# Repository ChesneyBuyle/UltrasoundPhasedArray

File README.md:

# UltrasoundPhasedArray
 Ultrasound phased array for directional transmission: construction, embedded software and python implementation

## General specifications
A low-cost, narrowband ultrasound phased array system for narrowbeam transmission is presented. 

The design features wide bandwidth MEMS loudspeakers (UT-P 2019, USound) with very small dimensions (5 x 7 mm). Dense loudspeaker arrays with small interelement spacing can be constructed, enabling grating lobe free beam patterns at high frequency. The current prototype can support up to 64 MEMS speakers. The amplitude and phase of each loudspeaker stage can be controlled with high resolution, respectively with 10-bit and 12-bit. The array itself is constructed using a 3D printer. 

## System overview

Block diagram of the prototype:

The loudspeaker array is controlled by an external computer. The phase delays and amplitudes of the loudspeaker stages are calculated according to the desired ultrasound beam pattern in Python. Next, these parameters are sent to a controller board, which consists of a NUCLEO-H743ZI2 microcontroller board and custom signal distribution PCB. 
* The microcontroller sends the transducer stage parameters to the corresponding DSP boards. The DSP boards contain the signal generation and amplifier hardware blocks of the loudspeaker stages. 
* The microcontroller uses the signal distribution board to distribute a common clock signal to the DSP boards (for phase coherence) and it ensures communication to the correct hardware blocks. 

## Folder structure
* The *3D prints* folder contains the necessary STL-files to print the array. The loudspeakers should first be placed inside the *holder part (part 1)*. Next, the *cover part (part 2)* can be attached to the back of the array (side with connections on the MEMS loudspeakers) using M2 bolts. This keeps the MEMS loudspeakers in place when soldering the signal wires. Hence, now you should be able to solder the signal wires to the loudspeaker elements. We used very thin 0.25mm coated copper wire, because the loudspeaker connections are very fragile. Finally, we placed a thin layer of acoustic foam on the back of array and kept it into place using the *wire cover part (part 3)*. It also ensures that the signal wires and thus MEMS loudspeakers do not move anymore. 

* The *Python* folder contains the Python scripts for control over the transducer stages (controller.py and main.py). Furthermore, the Python scripts for sampling of the microphone signal (daq.py), stepper motor control (stepper.py) and plotting (plotter.py) are also available. Note that some paths may need to updated before the code runs correctly.

* The *PCB design files* folder contains the schematic and board files of the custom signal distribution and DSP boards (DDS, VGA and power amplifier). These were designed in Eagle. 

* The *Controller board code* contains the embedded code for the NUCLEO-H743ZI2 microcontroller board.

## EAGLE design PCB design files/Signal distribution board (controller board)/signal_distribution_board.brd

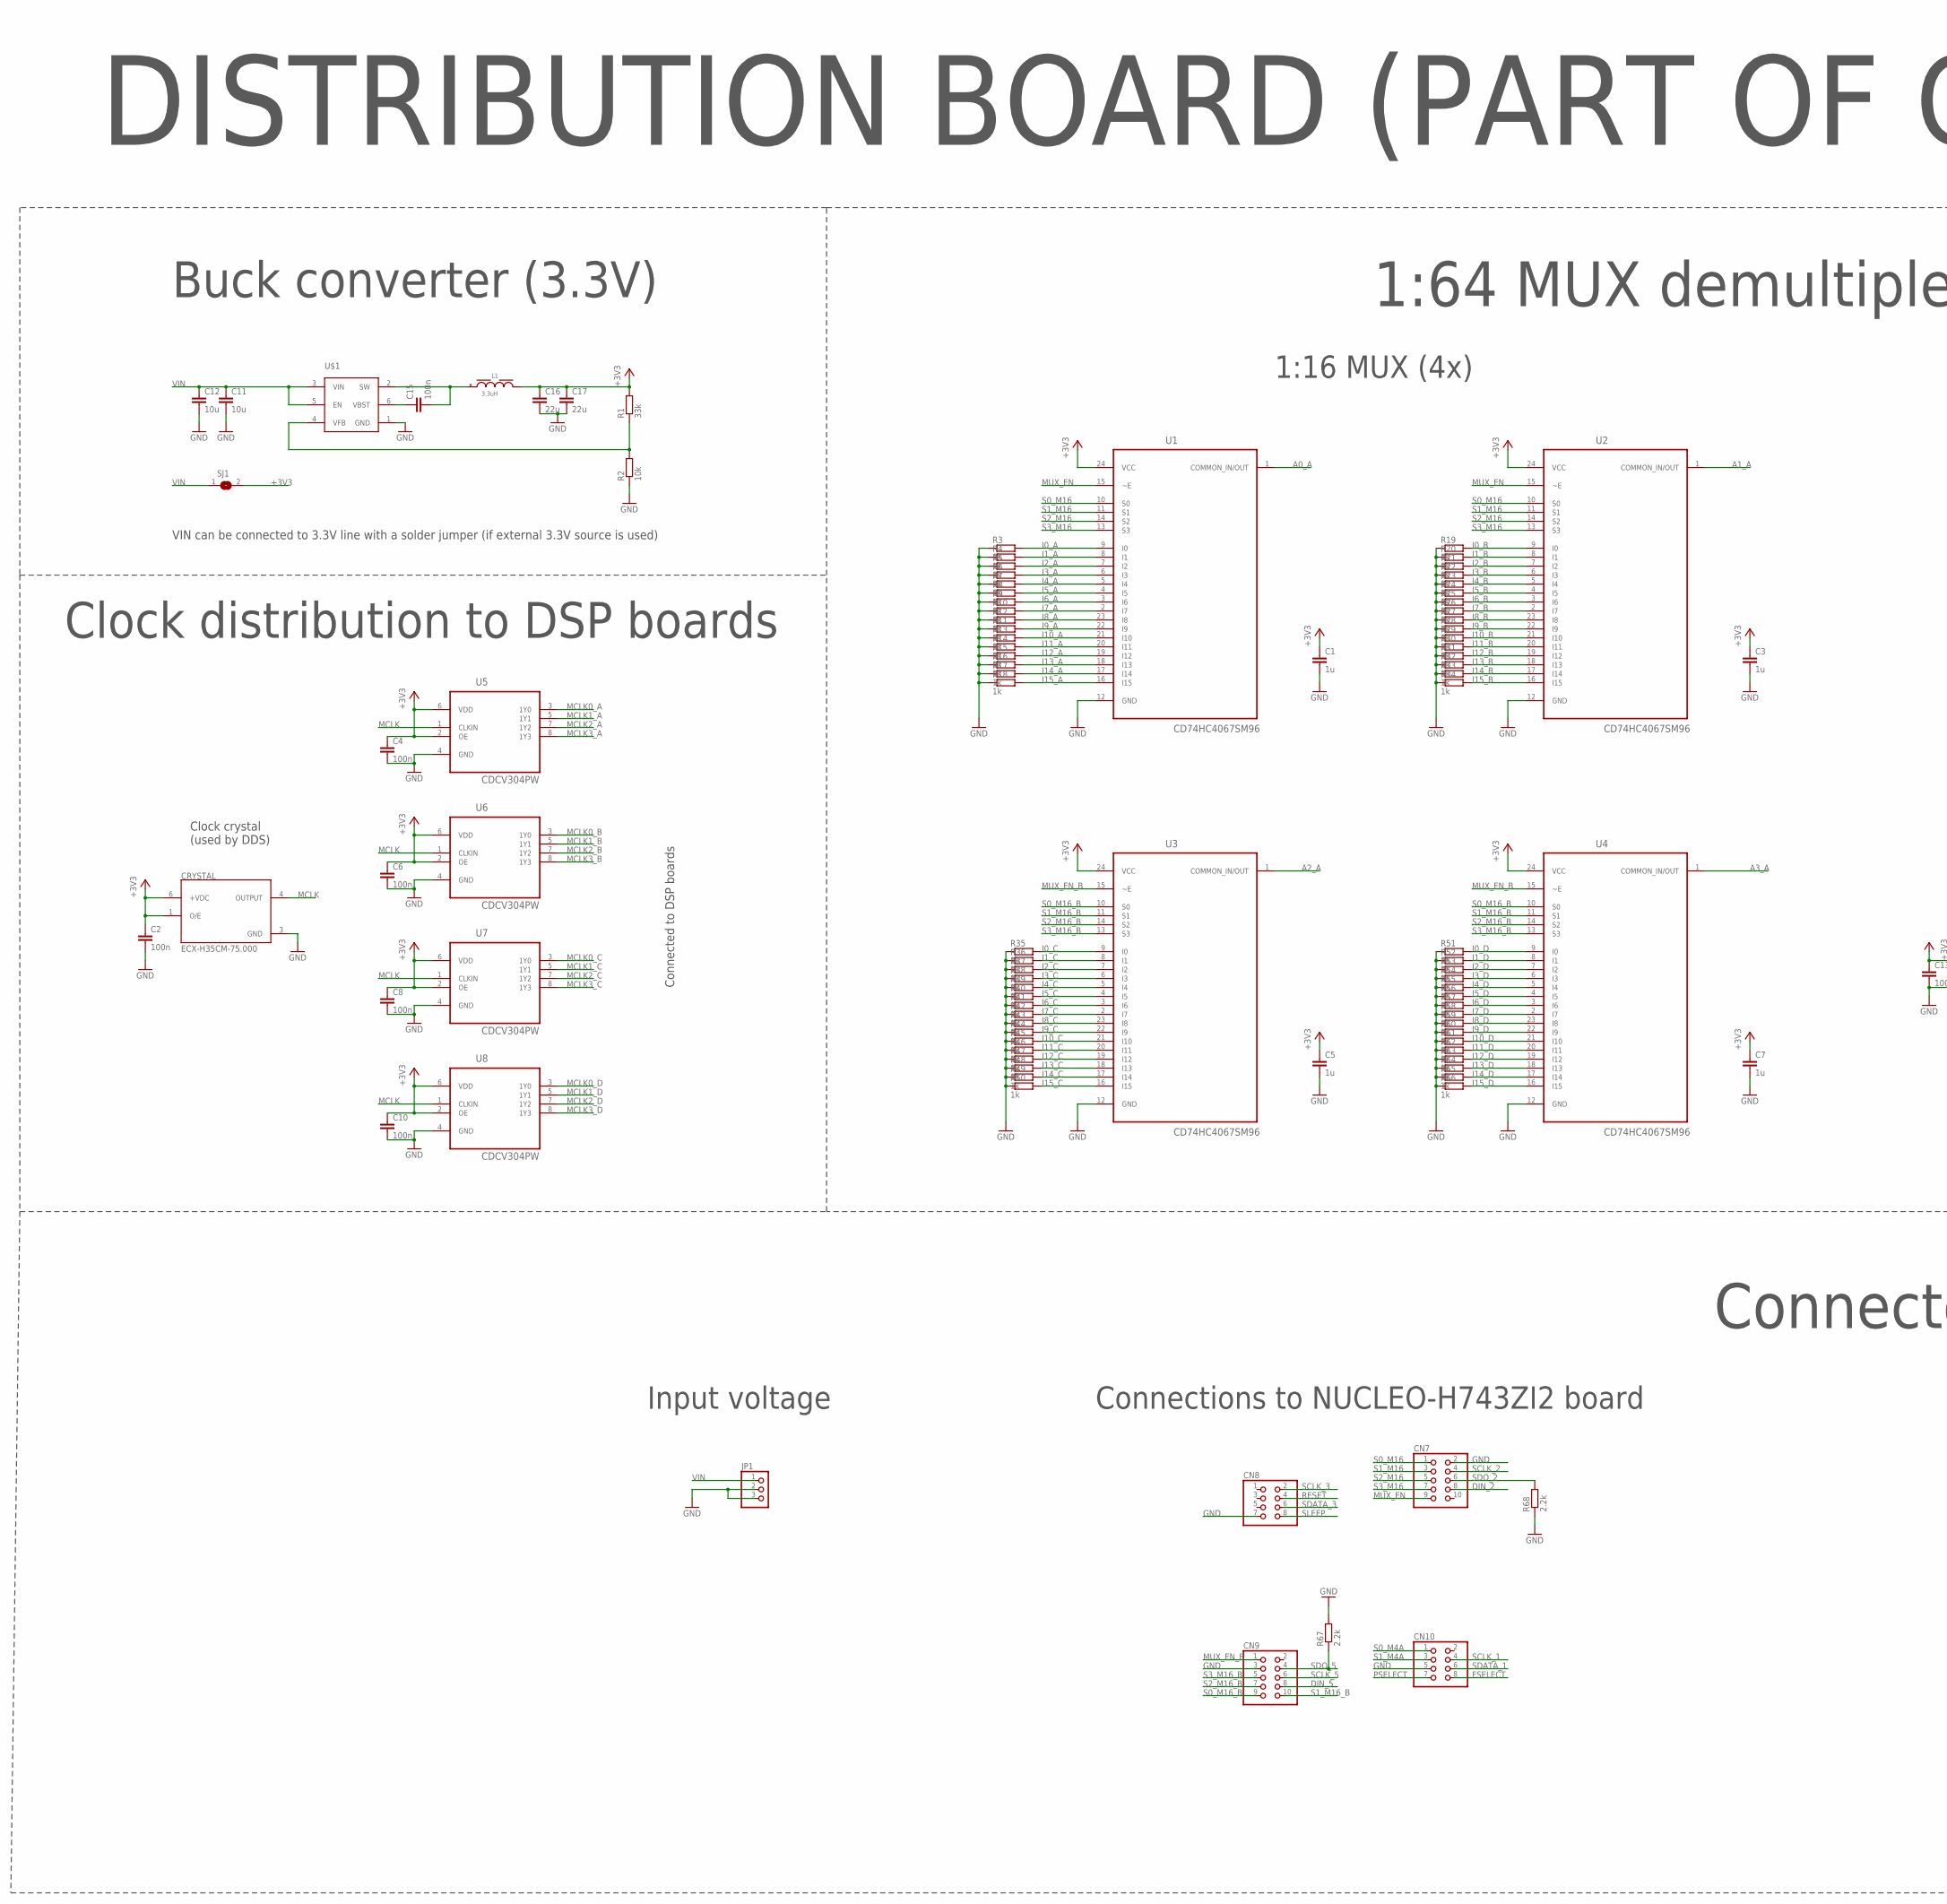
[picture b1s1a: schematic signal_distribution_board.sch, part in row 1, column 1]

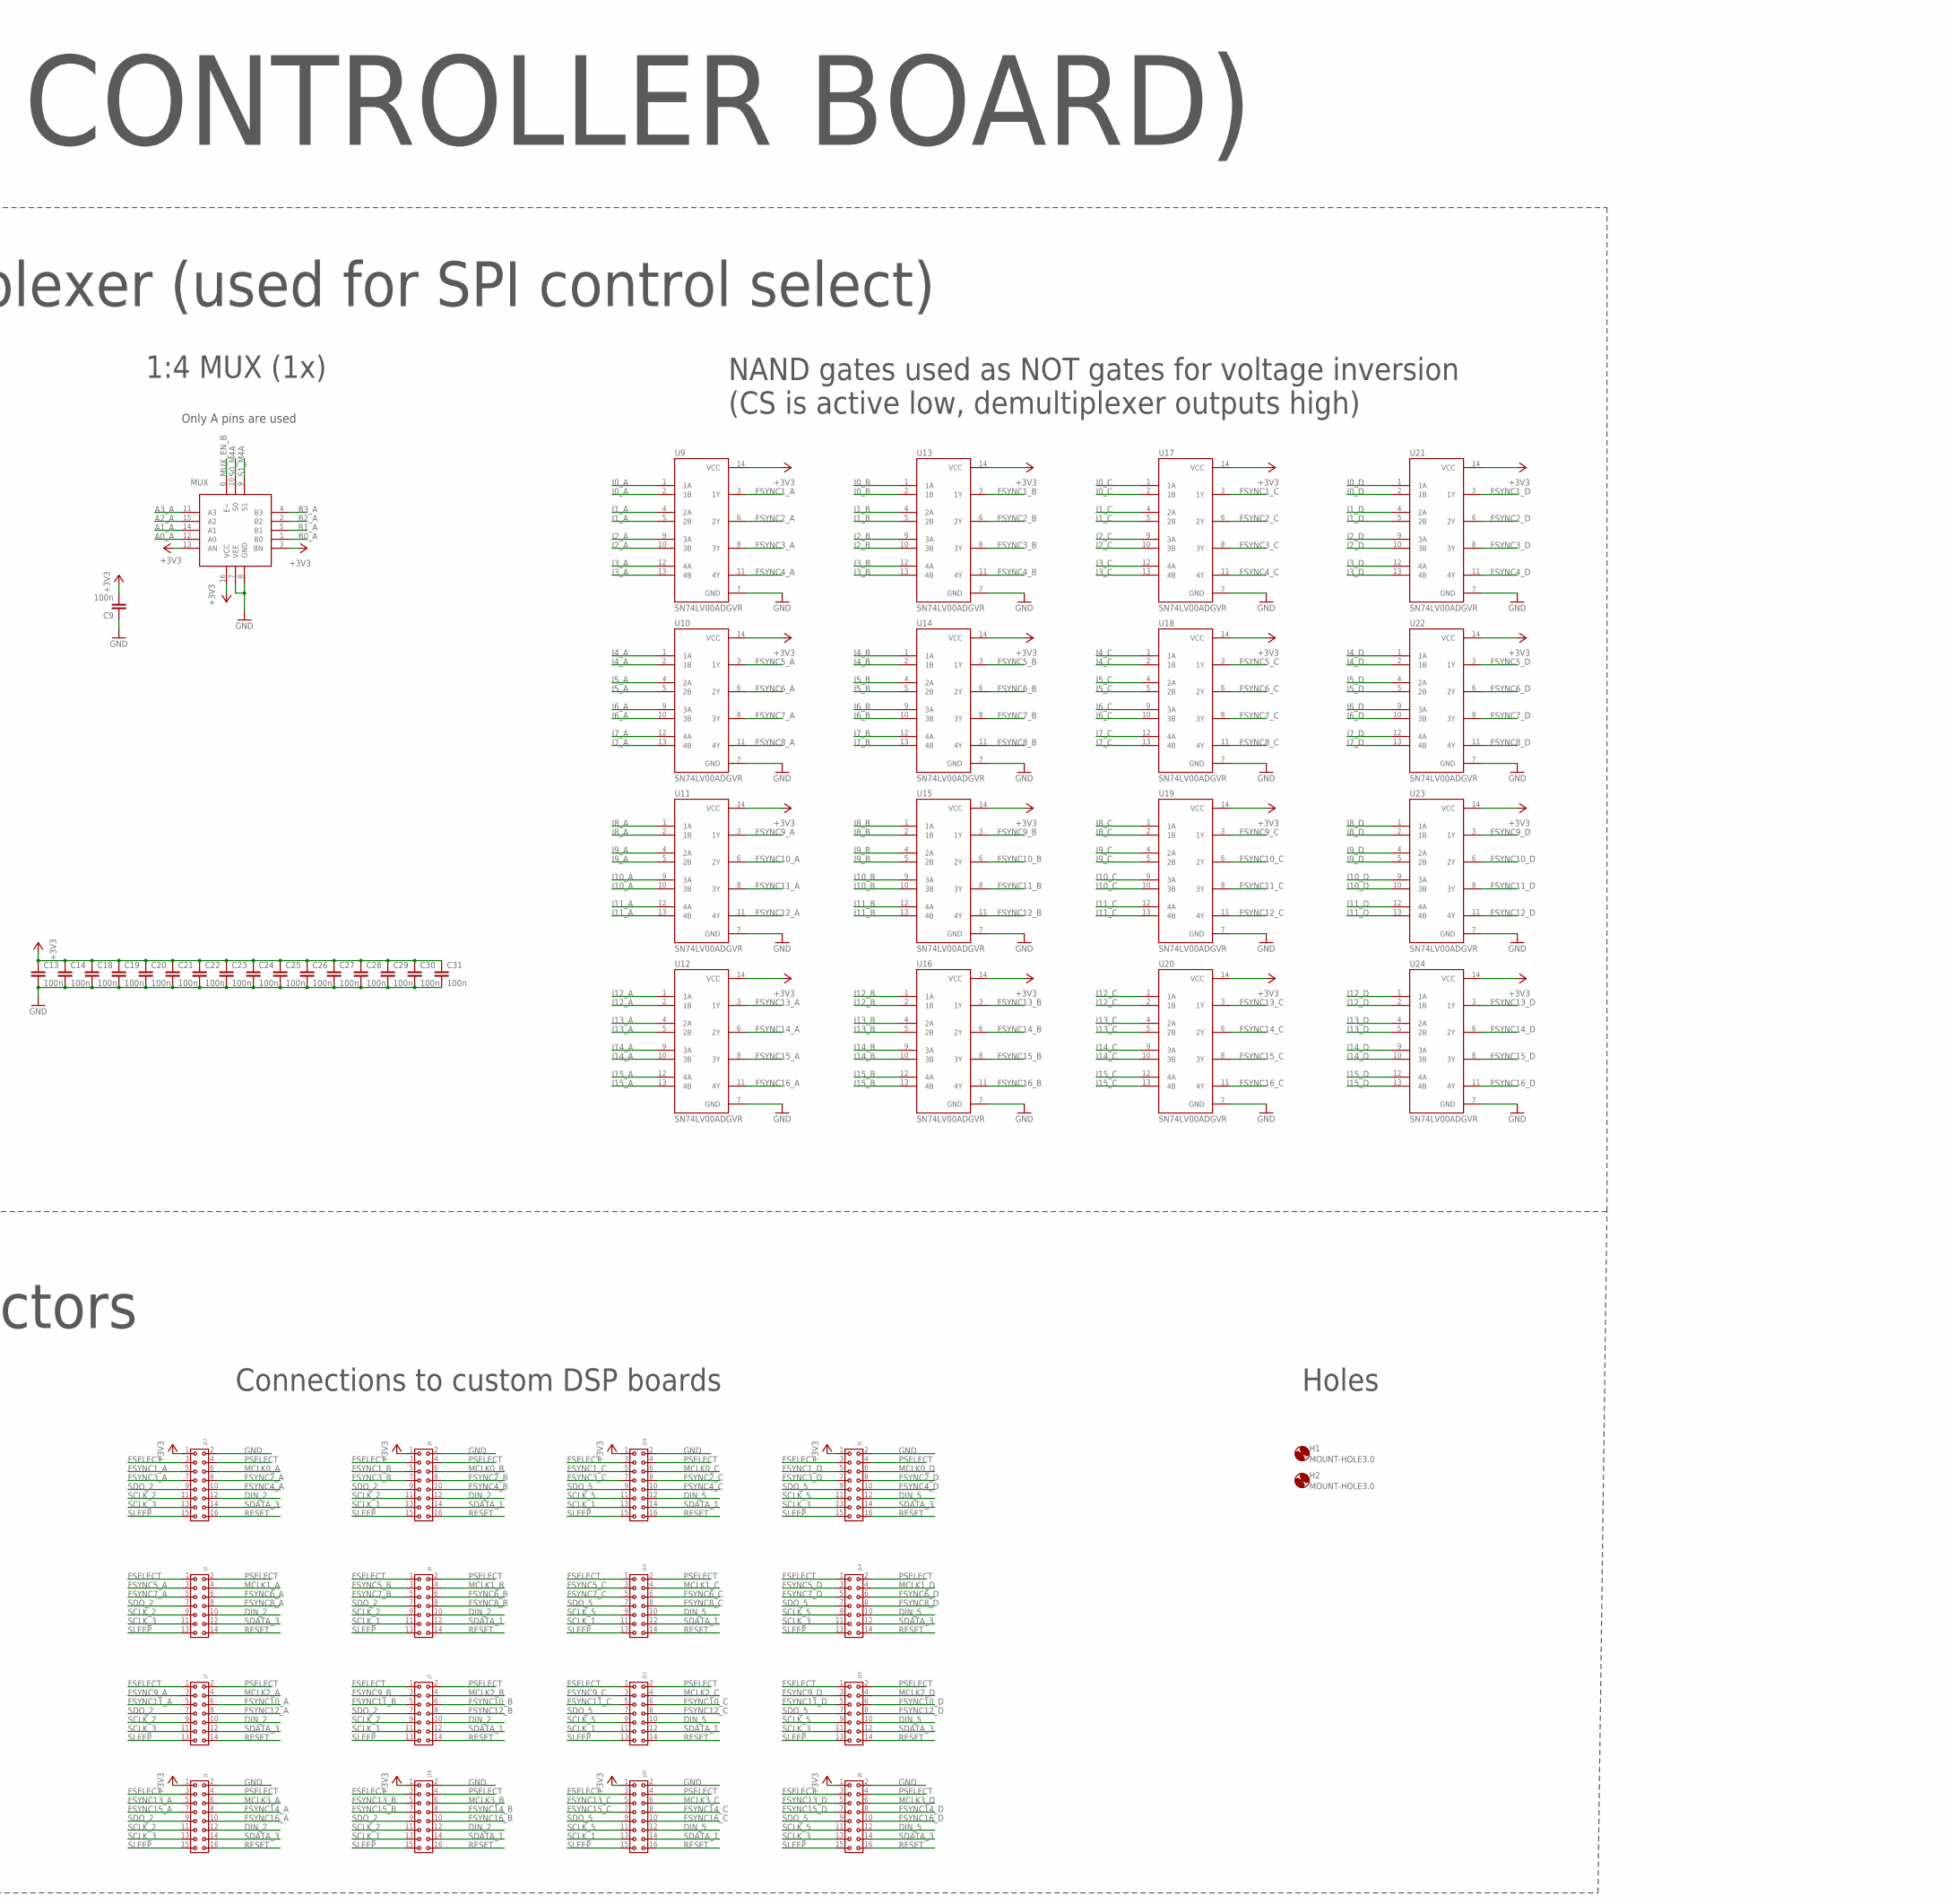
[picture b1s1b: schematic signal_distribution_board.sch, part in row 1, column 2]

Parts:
C1, C3, C5, C7: 1u; C0603
C2, C4, C6, C8, C9, C10, C13, C14, C15, C18, C19, C20, C21, C22, C23, C24, C25, C26, C27, C28, C29, C30, C31: 100n; C0603
C11, C12: 10u; C0805
C16, C17: 22u; C1206
CN7, CN9: PINHD-2X5; 2X05
CN8, CN10: PINHD-2X4; 2X04
CRYSTAL: ECX-H35CM-75.000; OSC_ECX-H35CM-75.000
H1, H2: MOUNT-HOLE3.0; 3,0
J1, J4, J5, J8, J17, J18, J19, J20: 6130XX243121_613016243121; 613016243121
J2, J3, J6, J7, J10, J11, J14, J15: 6130XX243121_613014243121; 613014243121
JP1: PINHD-1X3; 1X03
L1: 3.3uH; WE-PD_7345P
MUX: CD74HC4052M96; SOIC127P600X175-16N
R1: 33k; R0603
R2: 10k; R0603
R3, R4, R5, R6, R7, R8, R9, R10, R11, R12, R13, R14, R15, R16, R17, R18, R19, R20, R21, R22, R23, R24, R25, R26, R27, R28, R29, R30, R31, R32, R33, R34, R35, R36, R37, R38, R39, R40, R41, R42, R43, R44, R45, R46, R47, R48, R49, R50, R51, R52, R53, R54, R55, R56, R57, R58, R59, R60, R61, R62, R63, R64, R65, R66: 1k; R0603
R67, R68: 2.2k; R0805
SJ1: SJ
U1, U2, U3, U4: CD74HC4067SM96; SOP65P780X200-24N
U5, U6, U7, U8: CDCV304PW; SOP65P640X120-8N
U9, U10, U11, U12, U13, U14, U15, U16, U17, U18, U19, U20, U21, U22, U23, U24: SN74LV00ADGVR; SOP40P640X120-14N
U$1: TPS562209; SOT95P280X110-6N

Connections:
+3V3: C1.1, C2.1, C3.1, C4.1, C5.1, C6.1, C7.1, C8.1, C9.2, C10.1, C13.1, C14.1, C16.1, C17.1, C18.1, C19.1, C20.1, C21.1, C22.1, C23.1, C24.1, C25.1, C26.1, C27.1, C28.1, C29.1, C30.1, C31.1, CRYSTAL.1 (O/E), CRYSTAL.6 (+VDC), J1.1, J4.1, J5.1, J8.1, J17.1, J18.1, J19.1, J20.1, L1.2, MUX.3 (BN), MUX.13 (AN), MUX.16 (VCC), R1.2, SJ1.2, U1.24 (VCC), U2.24 (VCC), U3.24 (VCC), U4.24 (VCC), U5.2 (OE), U5.6 (VDD), U6.2 (OE), U6.6 (VDD), U7.2 (OE), U7.6 (VDD), U8.2 (OE), U8.6 (VDD), U9.14 (VCC), U10.14 (VCC), U11.14 (VCC), U12.14 (VCC), U13.14 (VCC), U14.14 (VCC), U15.14 (VCC), U16.14 (VCC), U17.14 (VCC), U18.14 (VCC), U19.14 (VCC), U20.14 (VCC), U21.14 (VCC), U22.14 (VCC), U23.14 (VCC), U24.14 (VCC)
A0_A: MUX.12 (A0), U1.1 (COMMON_IN/OUT)
A1_A: MUX.14 (A1), U2.1 (COMMON_IN/OUT)
A2_A: MUX.15 (A2), U3.1 (COMMON_IN/OUT)
A3_A: MUX.11 (A3), U4.1 (COMMON_IN/OUT)
B0_A: MUX.1 (B0)
B1_A: MUX.5 (B1)
B2_A: MUX.2 (B2)
B3_A: MUX.4 (B3)
DIN_2: CN7.8, J1.12, J2.10, J3.10, J4.12, J6.10, J7.10, J17.12, J18.12
DIN_5: CN9.8, J5.12, J8.12, J10.10, J11.10, J14.10, J15.10, J19.12, J20.12
FSELECT: CN10.8, J1.3, J2.1, J3.1, J4.3, J5.3, J6.1, J7.1, J8.3, J10.1, J11.1, J14.1, J15.1, J17.3, J18.3, J19.3, J20.3
FSYNC1_A: J17.5, U9.3 (1Y)
FSYNC1_B: J4.5, U13.3 (1Y)
FSYNC1_C: J19.5, U17.3 (1Y)
FSYNC1_D: J5.5, U21.3 (1Y)
FSYNC2_A: J17.8, U9.6 (2Y)
FSYNC2_B: J4.8, U13.6 (2Y)
FSYNC2_C: J19.8, U17.6 (2Y)
FSYNC2_D: J5.8, U21.6 (2Y)
FSYNC3_A: J17.7, U9.8 (3Y)
FSYNC3_B: J4.7, U13.8 (3Y)
FSYNC3_C: J19.7, U17.8 (3Y)
FSYNC3_D: J5.7, U21.8 (3Y)
FSYNC4_A: J17.10, U9.11 (4Y)
FSYNC4_B: J4.10, U13.11 (4Y)
FSYNC4_C: J19.10, U17.11 (4Y)
FSYNC4_D: J5.10, U21.11 (4Y)
FSYNC5_A: J2.3, U10.3 (1Y)
FSYNC5_B: J6.3, U14.3 (1Y)
FSYNC5_C: J10.3, U18.3 (1Y)
FSYNC5_D: J14.3, U22.3 (1Y)
FSYNC6_A: J2.6, U10.6 (2Y)
FSYNC6_B: J6.6, U14.6 (2Y)
FSYNC6_C: J10.6, U18.6 (2Y)
FSYNC6_D: J14.6, U22.6 (2Y)
FSYNC7_A: J2.5, U10.8 (3Y)
FSYNC7_B: J6.5, U14.8 (3Y)
FSYNC7_C: J10.5, U18.8 (3Y)
FSYNC7_D: J14.5, U22.8 (3Y)
FSYNC8_A: J2.8, U10.11 (4Y)
FSYNC8_B: J6.8, U14.11 (4Y)
FSYNC8_C: J10.8, U18.11 (4Y)
FSYNC8_D: J14.8, U22.11 (4Y)
FSYNC9_A: J3.3, U11.3 (1Y)
FSYNC9_B: J7.3, U15.3 (1Y)
FSYNC9_C: J11.3, U19.3 (1Y)
FSYNC9_D: J15.3, U23.3 (1Y)
FSYNC10_A: J3.6, U11.6 (2Y)
FSYNC10_B: J7.6, U15.6 (2Y)
FSYNC10_C: J11.6, U19.6 (2Y)
FSYNC10_D: J15.6, U23.6 (2Y)
FSYNC11_A: J3.5, U11.8 (3Y)
FSYNC11_B: J7.5, U15.8 (3Y)
FSYNC11_C: J11.5, U19.8 (3Y)
FSYNC11_D: J15.5, U23.8 (3Y)
FSYNC12_A: J3.8, U11.11 (4Y)
FSYNC12_B: J7.8, U15.11 (4Y)
FSYNC12_C: J11.8, U19.11 (4Y)
FSYNC12_D: J15.8, U23.11 (4Y)
FSYNC13_A: J1.5, U12.3 (1Y)
FSYNC13_B: J18.5, U16.3 (1Y)
FSYNC13_C: J20.5, U20.3 (1Y)
FSYNC13_D: J8.5, U24.3 (1Y)
FSYNC14_A: J1.8, U12.6 (2Y)
FSYNC14_B: J18.8, U16.6 (2Y)
FSYNC14_C: J20.8, U20.6 (2Y)
FSYNC14_D: J8.8, U24.6 (2Y)
FSYNC15_A: J1.7, U12.8 (3Y)
FSYNC15_B: J18.7, U16.8 (3Y)
FSYNC15_C: J20.7, U20.8 (3Y)
FSYNC15_D: J8.7, U24.8 (3Y)
FSYNC16_A: J1.10, U12.11 (4Y)
FSYNC16_B: J18.10, U16.11 (4Y)
FSYNC16_C: J20.10, U20.11 (4Y)
FSYNC16_D: J8.10, U24.11 (4Y)
GND: C1.2, C2.2, C3.2, C4.2, C5.2, C6.2, C7.2, C8.2, C9.1, C10.2, C11.2, C12.2, C13.2, C14.2, C16.2, C17.2, C18.2, C19.2, C20.2, C21.2, C22.2, C23.2, C24.2, C25.2, C26.2, C27.2, C28.2, C29.2, C30.2, C31.2, CN7.2, CN8.7, CN9.3, CN10.5, CRYSTAL.3 (GND), J1.2, J4.2, J5.2, J8.2, J17.2, J18.2, J19.2, J20.2, JP1.2, JP1.3, MUX.7 (VEE), MUX.8 (GND), R2.1, R3.1, R4.1, R5.1, R6.1, R7.1, R8.1, R9.1, R10.1, R11.1, R12.1, R13.1, R14.1, R15.1, R16.1, R17.1, R18.1, R19.1, R20.1, R21.1, R22.1, R23.1, R24.1, R25.1, R26.1, R27.1, R28.1, R29.1, R30.1, R31.1, R32.1, R33.1, R34.1, R35.1, R36.1, R37.1, R38.1, R39.1, R40.1, R41.1, R42.1, R43.1, R44.1, R45.1, R46.1, R47.1, R48.1, R49.1, R50.1, R51.1, R52.1, R53.1, R54.1, R55.1, R56.1, R57.1, R58.1, R59.1, R60.1, R61.1, R62.1, R63.1, R64.1, R65.1, R66.1, R67.2, R68.1, U1.12 (GND), U2.12 (GND), U3.12 (GND), U4.12 (GND), U5.4 (GND), U6.4 (GND), U7.4 (GND), U8.4 (GND), U9.7 (GND), U10.7 (GND), U11.7 (GND), U12.7 (GND), U13.7 (GND), U14.7 (GND), U15.7 (GND), U16.7 (GND), U17.7 (GND), U18.7 (GND), U19.7 (GND), U20.7 (GND), U21.7 (GND), U22.7 (GND), U23.7 (GND), U24.7 (GND), U$1.1 (GND)
I0_A: R3.2, U1.9 (I0), U9.1 (1A), U9.2 (1B)
I0_B: R19.2, U2.9 (I0), U13.1 (1A), U13.2 (1B)
I0_C: R35.2, U3.9 (I0), U17.1 (1A), U17.2 (1B)
I0_D: R51.2, U4.9 (I0), U21.1 (1A), U21.2 (1B)
I1_A: R4.2, U1.8 (I1), U9.4 (2A), U9.5 (2B)
I1_B: R20.2, U2.8 (I1), U13.4 (2A), U13.5 (2B)
I1_C: R36.2, U3.8 (I1), U17.4 (2A), U17.5 (2B)
I1_D: R52.2, U4.8 (I1), U21.4 (2A), U21.5 (2B)
I2_A: R5.2, U1.7 (I2), U9.9 (3A), U9.10 (3B)
I2_B: R21.2, U2.7 (I2), U13.9 (3A), U13.10 (3B)
I2_C: R37.2, U3.7 (I2), U17.9 (3A), U17.10 (3B)
I2_D: R53.2, U4.7 (I2), U21.9 (3A), U21.10 (3B)
I3_A: R6.2, U1.6 (I3), U9.12 (4A), U9.13 (4B)
I3_B: R22.2, U2.6 (I3), U13.12 (4A), U13.13 (4B)
I3_C: R38.2, U3.6 (I3), U17.12 (4A), U17.13 (4B)
I3_D: R54.2, U4.6 (I3), U21.12 (4A), U21.13 (4B)
I4_A: R7.2, U1.5 (I4), U10.1 (1A), U10.2 (1B)
I4_B: R23.2, U2.5 (I4), U14.1 (1A), U14.2 (1B)
I4_C: R39.2, U3.5 (I4), U18.1 (1A), U18.2 (1B)
I4_D: R55.2, U4.5 (I4), U22.1 (1A), U22.2 (1B)
I5_A: R8.2, U1.4 (I5), U10.4 (2A), U10.5 (2B)
I5_B: R24.2, U2.4 (I5), U14.4 (2A), U14.5 (2B)
I5_C: R40.2, U3.4 (I5), U18.4 (2A), U18.5 (2B)
I5_D: R56.2, U4.4 (I5), U22.4 (2A), U22.5 (2B)
I6_A: R9.2, U1.3 (I6), U10.9 (3A), U10.10 (3B)
I6_B: R25.2, U2.3 (I6), U14.9 (3A), U14.10 (3B)
I6_C: R41.2, U3.3 (I6), U18.9 (3A), U18.10 (3B)
I6_D: R57.2, U4.3 (I6), U22.9 (3A), U22.10 (3B)
I7_A: R10.2, U1.2 (I7), U10.12 (4A), U10.13 (4B)
I7_B: R26.2, U2.2 (I7), U14.12 (4A), U14.13 (4B)
I7_C: R42.2, U3.2 (I7), U18.12 (4A), U18.13 (4B)
I7_D: R58.2, U4.2 (I7), U22.12 (4A), U22.13 (4B)
I8_A: R12.2, U1.23 (I8), U11.1 (1A), U11.2 (1B)
I8_B: R27.2, U2.23 (I8), U15.1 (1A), U15.2 (1B)
I8_C: R43.2, U3.23 (I8), U19.1 (1A), U19.2 (1B)
I8_D: R59.2, U4.23 (I8), U23.1 (1A), U23.2 (1B)
I9_A: R11.2, U1.22 (I9), U11.4 (2A), U11.5 (2B)
I9_B: R28.2, U2.22 (I9), U15.4 (2A), U15.5 (2B)
I9_C: R44.2, U3.22 (I9), U19.4 (2A), U19.5 (2B)
I9_D: R60.2, U4.22 (I9), U23.4 (2A), U23.5 (2B)
I10_A: R13.2, U1.21 (I10), U11.9 (3A), U11.10 (3B)
I10_B: R29.2, U2.21 (I10), U15.9 (3A), U15.10 (3B)
I10_C: R45.2, U3.21 (I10), U19.9 (3A), U19.10 (3B)
I10_D: R61.2, U4.21 (I10), U23.9 (3A), U23.10 (3B)
I11_A: R14.2, U1.20 (I11), U11.12 (4A), U11.13 (4B)
I11_B: R30.2, U2.20 (I11), U15.12 (4A), U15.13 (4B)
I11_C: R46.2, U3.20 (I11), U19.12 (4A), U19.13 (4B)
I11_D: R62.2, U4.20 (I11), U23.12 (4A), U23.13 (4B)
I12_A: R15.2, U1.19 (I12), U12.1 (1A), U12.2 (1B)
I12_B: R31.2, U2.19 (I12), U16.1 (1A), U16.2 (1B)
I12_C: R47.2, U3.19 (I12), U20.1 (1A), U20.2 (1B)
I12_D: R63.2, U4.19 (I12), U24.1 (1A), U24.2 (1B)
I13_A: R16.2, U1.18 (I13), U12.4 (2A), U12.5 (2B)
I13_B: R32.2, U2.18 (I13), U16.4 (2A), U16.5 (2B)
I13_C: R48.2, U3.18 (I13), U20.4 (2A), U20.5 (2B)
I13_D: R64.2, U4.18 (I13), U24.4 (2A), U24.5 (2B)
I14_A: R17.2, U1.17 (I14), U12.9 (3A), U12.10 (3B)
I14_B: R33.2, U2.17 (I14), U16.9 (3A), U16.10 (3B)
I14_C: R49.2, U3.17 (I14), U20.9 (3A), U20.10 (3B)
I14_D: R65.2, U4.17 (I14), U24.9 (3A), U24.10 (3B)
I15_A: R18.2, U1.16 (I15), U12.12 (4A), U12.13 (4B)
I15_B: R34.2, U2.16 (I15), U16.12 (4A), U16.13 (4B)
I15_C: R50.2, U3.16 (I15), U20.12 (4A), U20.13 (4B)
I15_D: R66.2, U4.16 (I15), U24.12 (4A), U24.13 (4B)
MCLK: CRYSTAL.4 (OUTPUT), U5.1 (CLKIN), U6.1 (CLKIN), U7.1 (CLKIN), U8.1 (CLKIN)
MCLK0_A: J17.6, U5.3 (1Y0)
MCLK0_B: J4.6, U6.3 (1Y0)
MCLK0_C: J19.6, U7.3 (1Y0)
MCLK0_D: J5.6, U8.3 (1Y0)
MCLK1_A: J2.4, U5.5 (1Y1)
MCLK1_B: J6.4, U6.5 (1Y1)
MCLK1_C: J10.4, U7.5 (1Y1)
MCLK1_D: J14.4, U8.5 (1Y1)
MCLK2_A: J3.4, U5.7 (1Y2)
MCLK2_B: J7.4, U6.7 (1Y2)
MCLK2_C: J11.4, U7.7 (1Y2)
MCLK2_D: J15.4, U8.7 (1Y2)
MCLK3_A: J1.6, U5.8 (1Y3)
MCLK3_B: J18.6, U6.8 (1Y3)
MCLK3_C: J20.6, U7.8 (1Y3)
MCLK3_D: J8.6, U8.8 (1Y3)
MUX_EN: CN7.9, U1.15 (~E), U2.15 (~E)
MUX_EN_B: CN9.1, MUX.6 (E~), U3.15 (~E), U4.15 (~E)
unnamed: C15.1, U$1.6 (VBST)
unnamed: R1.1, R2.2, U$1.4 (VFB)
unnamed: C15.2, L1.1, U$1.2 (SW)
PSELECT: CN10.7, J1.4, J2.2, J3.2, J4.4, J5.4, J6.2, J7.2, J8.4, J10.2, J11.2, J14.2, J15.2, J17.4, J18.4, J19.4, J20.4
RESET: CN8.4, J1.16, J2.14, J3.14, J4.16, J5.16, J6.14, J7.14, J8.16, J10.14, J11.14, J14.14, J15.14, J17.16, J18.16, J19.16, J20.16
S0_M4A: CN10.1, MUX.10 (S0)
S0_M16: CN7.1, U1.10 (S0), U2.10 (S0)
S0_M16_B: CN9.9, U3.10 (S0), U4.10 (S0)
S1_M4A: CN10.3, MUX.9 (S1)
S1_M16: CN7.3, U1.11 (S1), U2.11 (S1)
S1_M16_B: CN9.10, U3.11 (S1), U4.11 (S1)
S2_M16: CN7.5, U1.14 (S2), U2.14 (S2)
S2_M16_B: CN9.7, U3.14 (S2), U4.14 (S2)
S3_M16: CN7.7, U1.13 (S3), U2.13 (S3)
S3_M16_B: CN9.5, U3.13 (S3), U4.13 (S3)
SCLK_1: CN10.4, J4.13, J6.11, J7.11, J10.11, J11.11, J18.13, J19.13, J20.13
SCLK_2: CN7.4, J1.11, J2.9, J3.9, J4.11, J6.9, J7.9, J17.11, J18.11
SCLK_3: CN8.2, J1.13, J2.11, J3.11, J5.13, J8.13, J14.11, J15.11, J17.13
SCLK_5: CN9.6, J5.11, J8.11, J10.9, J11.9, J14.9, J15.9, J19.11, J20.11
SDATA_1: CN10.6, J4.14, J6.12, J7.12, J10.12, J11.12, J18.14, J19.14, J20.14
SDATA_3: CN8.6, J1.14, J2.12, J3.12, J5.14, J8.14, J14.12, J15.12, J17.14
SDO_2: CN7.6, J1.9, J2.7, J3.7, J4.9, J6.7, J7.7, J17.9, J18.9, R68.2
SDO_5: CN9.4, J5.9, J8.9, J10.7, J11.7, J14.7, J15.7, J19.9, J20.9, R67.1
SLEEP: CN8.8, J1.15, J2.13, J3.13, J4.15, J5.15, J6.13, J7.13, J8.15, J10.13, J11.13, J14.13, J15.13, J17.15, J18.15, J19.15, J20.15
VIN: C11.1, C12.1, JP1.1, SJ1.1, U$1.3 (VIN), U$1.5 (EN)

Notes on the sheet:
Clock distribution to DSP boards
Buck converter (3.3V)
Connectors
1:64 MUX demultiplexer (used for SPI control select)
VIN can be connected to 3.3V line with a solder jumper (if external 3.3V source is used)
Connected to DSP boards
Clock crystal (used by DDS)
1:16 MUX (4x)
1:4 MUX (1x)
Only A pins are used
NAND gates used as NOT gates for voltage inversion (CS is active low, demultiplexer outputs high)
Connections to NUCLEO-H743ZI2 board
Input voltage
Connections to custom DSP boards
Holes
DISTRIBUTION BOARD (PART OF CONTROLLER BOARD)

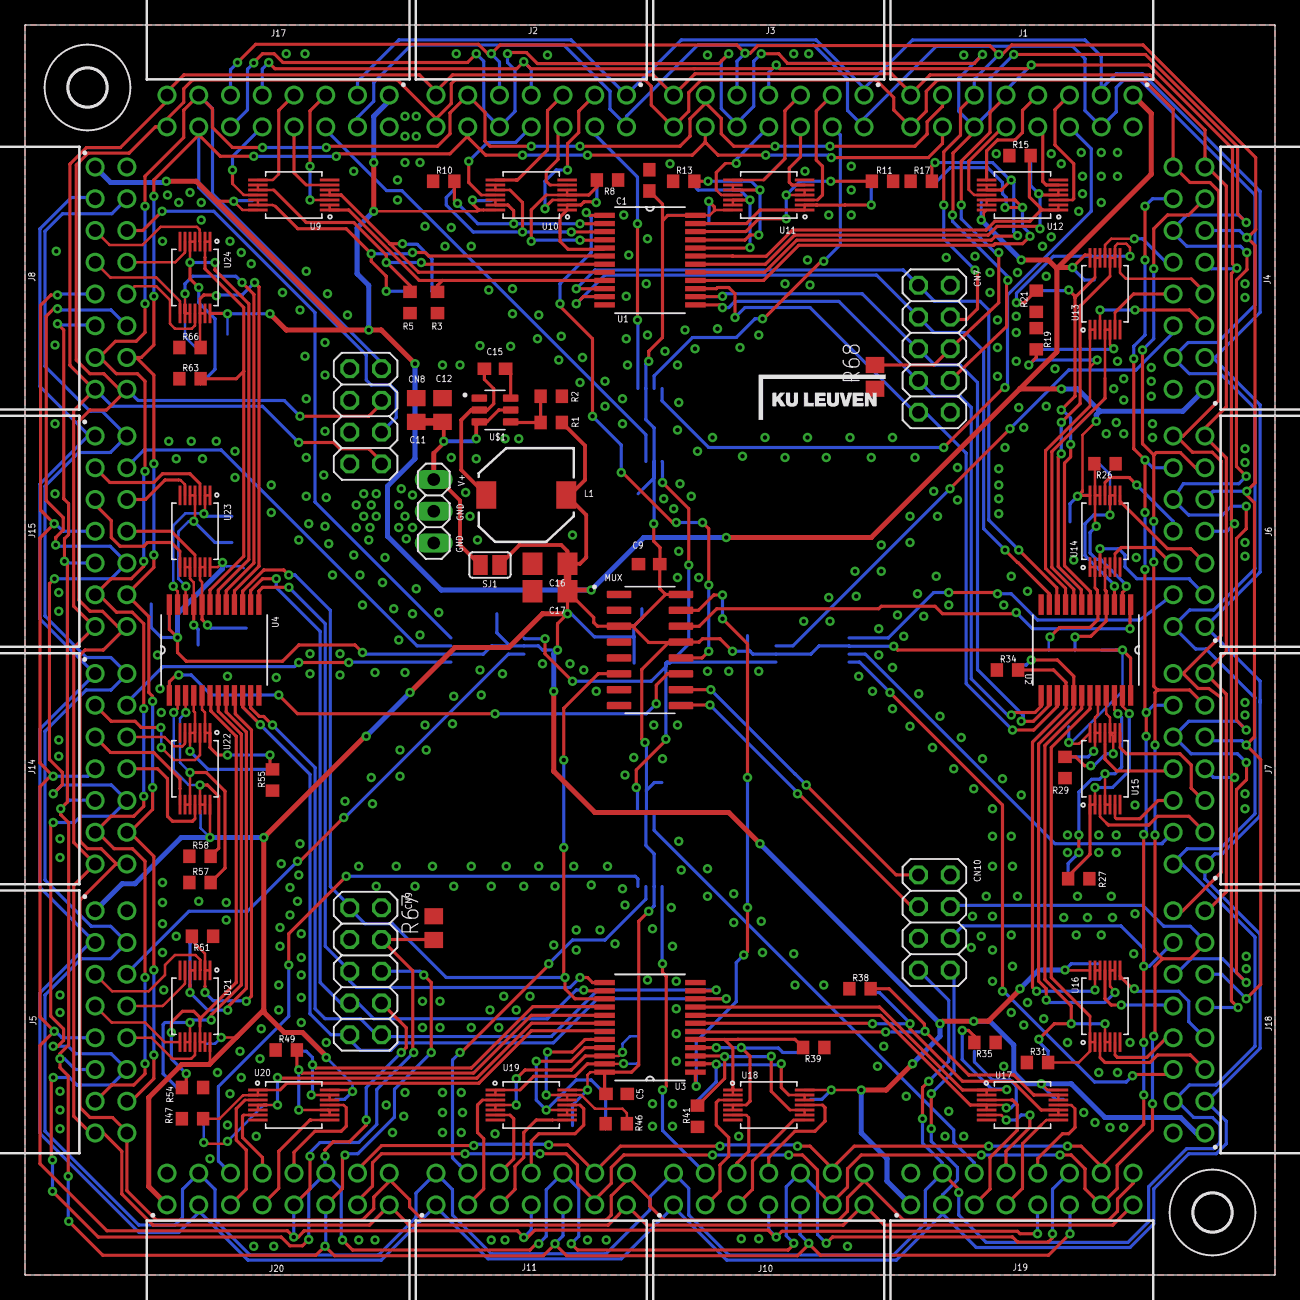
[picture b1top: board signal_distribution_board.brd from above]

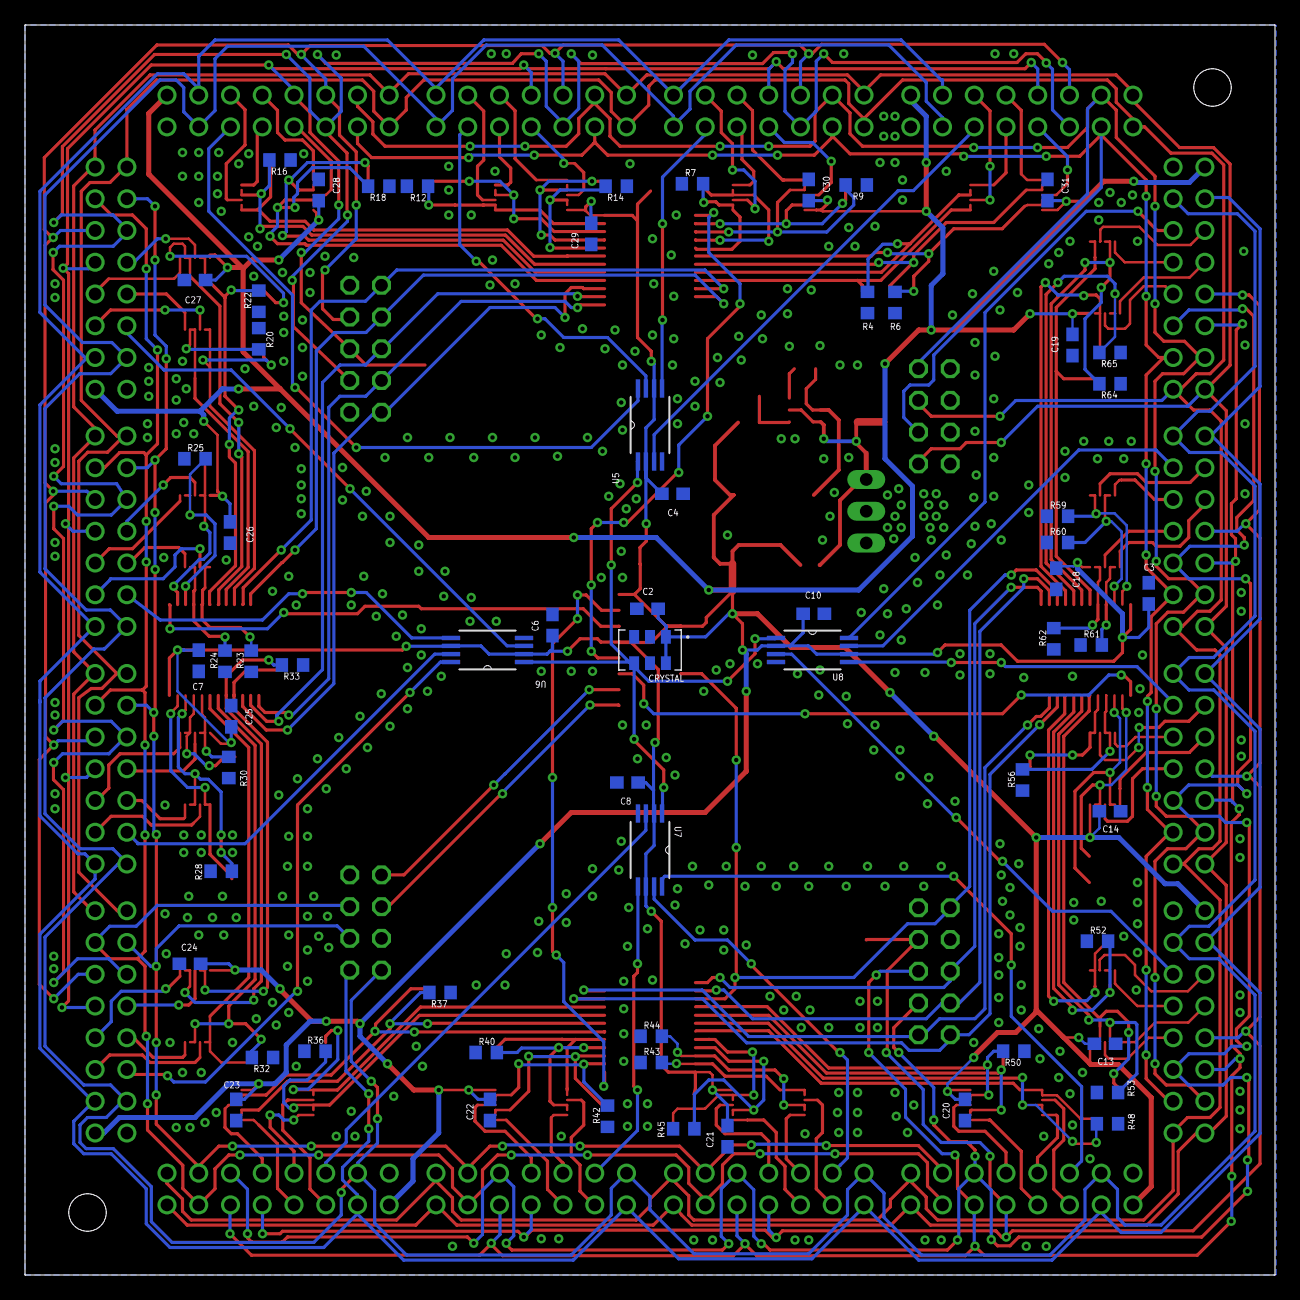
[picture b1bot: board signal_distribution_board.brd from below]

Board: 2 copper layers, 100.0 x 100.0 mm, 151 parts (63 on the bottom side), 181 nets.

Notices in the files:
parts and their libraries:
61301621021_Eagle_WR-PHD_rev19a: Copyright: Würth Elektronik
